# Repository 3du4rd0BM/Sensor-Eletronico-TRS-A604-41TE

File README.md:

# Sensor Eletrônico TRS A604 41TE
 Sensor TRS do câmbio A604 41TE controlado eletrônicamente por arduino nano.

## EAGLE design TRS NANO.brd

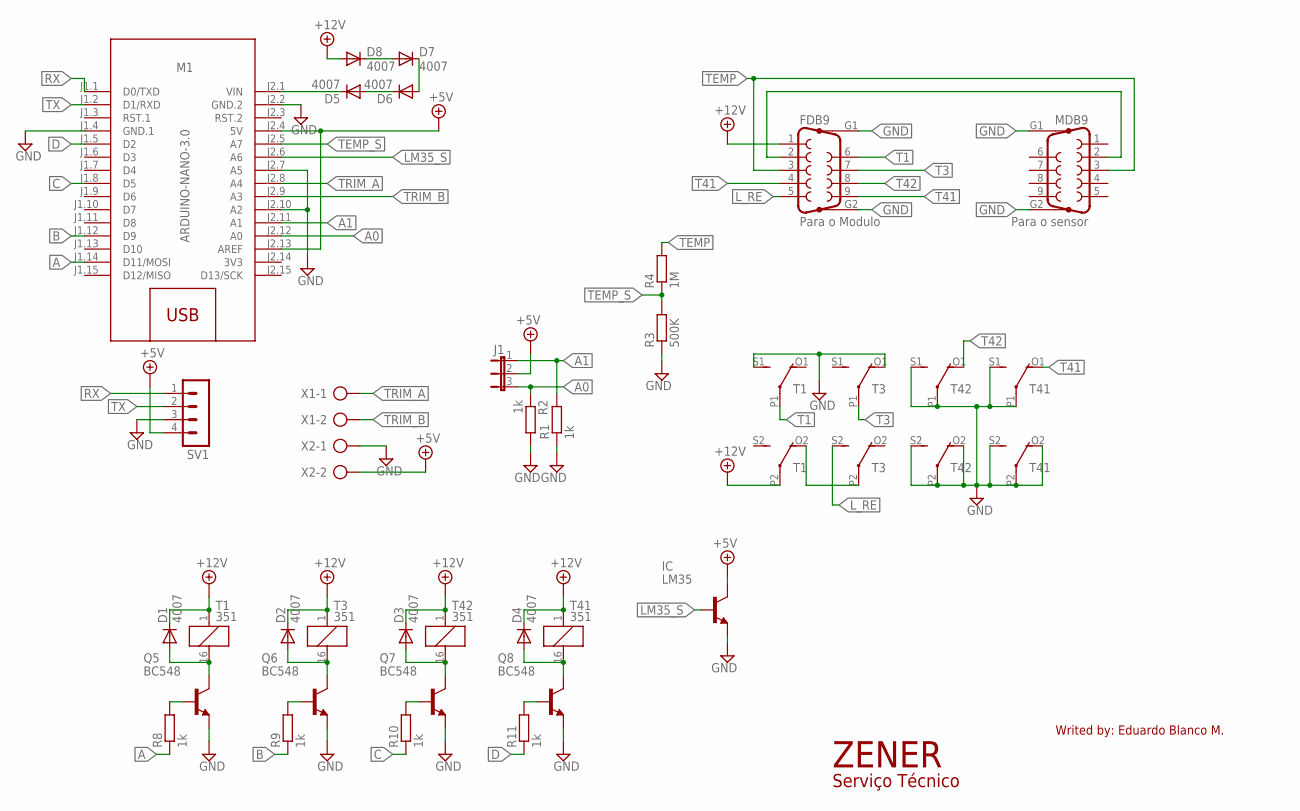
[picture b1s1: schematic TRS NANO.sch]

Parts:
D1, D2, D3, D4, D5, D6, D7, D8: 4007; D-7.5
FDB9: Para o Modulo; F09HP
IC: LM35; TO92-EBC
J1: JP2W
M1: ARDUINO-NANO-3.0
MDB9: Para o sensor; F09HP
Q5, Q6, Q7, Q8: BC548; TO92-EBC
R1: 1k; 0207/10
R2: 1k; 0207/7
R3: 500K; 0207/7
R4: 1M; 0207/15
R8, R9, R10, R11: 1k; 0207/5V
SV1: MA04-1
T1, T3, T41, T42: 351
X1, X2: AK500/2

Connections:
3V3: M1.J2.14 (3V3)
+5V: IC.C, J1.2, M1.J2.4 (5V), M1.J2.13 (AREF), SV1.4, X2.2
+12V: D1.C, D2.C, D3.C, D4.C, D8.A, FDB9.1, T1.1, T1.P2, T3.1, T41.1, T42.1
A: M1.J1.14 (D11/MOSI), R8.1
A0: J1.3, M1.J2.12 (A0), R2.1
A1: J1.1, M1.J2.11 (A1), R1.2
B: M1.J1.12 (D9), R9.1
C: M1.J1.8 (D5), R10.1
D: M1.J1.5 (D2), R11.1
GND: FDB9.G1, FDB9.G2, IC.E, M1.J1.4 (GND.1), M1.J2.2 (GND.2), M1.J2.7 (A5), M1.J2.10 (A2), MDB9.G1, MDB9.G2, Q5.E, Q6.E, Q7.E, Q8.E, R1.1, R2.2, R3.1, SV1.3, T1.S1 (S), T3.O1 (O), T41.O2 (O), T41.P1, T41.P2, T41.S1 (S), T41.S2 (S), T42.O2 (O), T42.P1, T42.P2, T42.S1 (S), T42.S2 (S), X2.1
LM35_S: IC.B, M1.J2.6 (A6)
L_RE: FDB9.5, T3.S2 (S)
unnamed: T1.O2 (O), T3.P2
unnamed: Q6.B, R9.2
unnamed: Q7.B, R10.2
unnamed: Q8.B, R11.2
unnamed: D5.C, M1.J2.1 (VIN)
unnamed: Q5.B, R8.2
unnamed: FDB9.2, MDB9.2
unnamed: D5.A, D6.C
unnamed: D6.A, D7.C
unnamed: D1.A, Q5.C, T1.16 (2)
unnamed: D2.A, Q6.C, T3.16 (2)
unnamed: D3.A, Q7.C, T42.16 (2)
unnamed: D4.A, Q8.C, T41.16 (2)
unnamed: D7.A, D8.C
RX: M1.J1.1 (D0/TXD), SV1.1
T1: FDB9.6, T1.P1
T3: FDB9.7, T3.P1
T41: FDB9.4, FDB9.9, T41.O1 (O)
T42: FDB9.8, T42.O1 (O)
TEMP: FDB9.3, MDB9.3, R4.2
TEMP_S: M1.J2.5 (A7), R3.2, R4.1
TRIM_A: M1.J2.8 (A4), X1.1
TRIM_B: M1.J2.9 (A3), X1.2
TX: M1.J1.2 (D1/RXD), SV1.2

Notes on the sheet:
Writed by: Eduardo Blanco M.
ZENER
Serviço Técnico

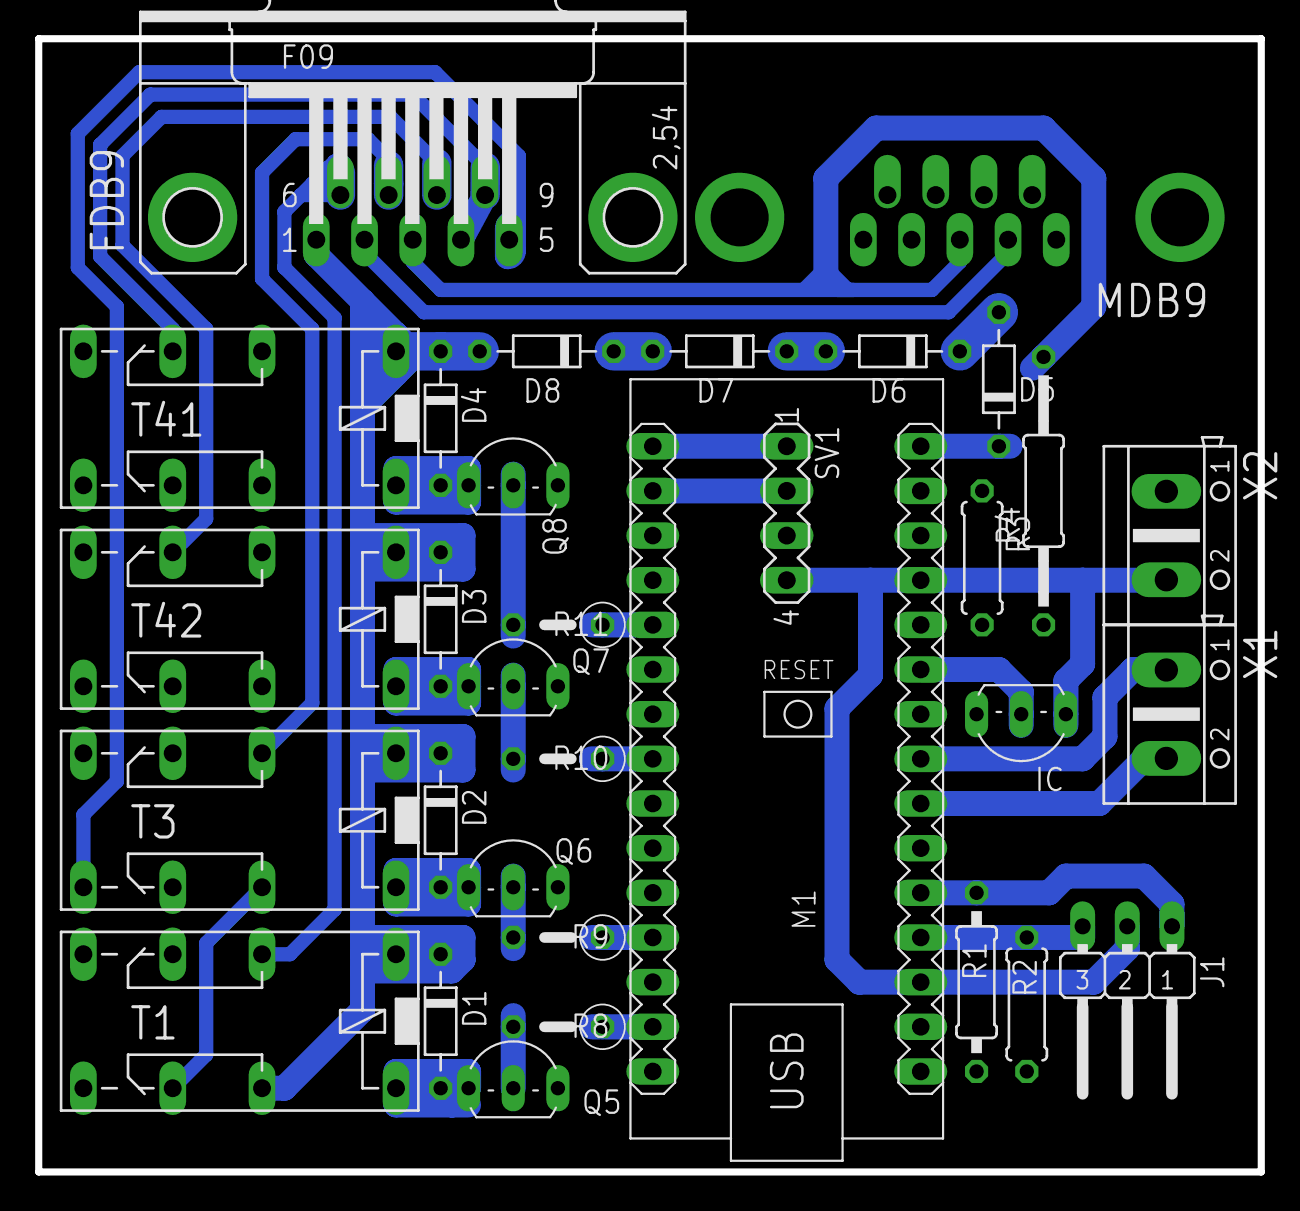
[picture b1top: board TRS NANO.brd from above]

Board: 2 copper layers, 69.5 x 64.5 mm, 32 parts (1 on the bottom side), 35 nets.

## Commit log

2024-06-17 correto
2024-06-17 PDFs
2024-07-06 elimina LM35
2024-07-08 atualiza placa
2024-08-05 Manual
2024-10-28 minifit

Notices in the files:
parts and their libraries:
diy-modules: Released under the Creative Commons Attribution 4.0 International License: http://creativecommons.org/licenses/by/4.0
